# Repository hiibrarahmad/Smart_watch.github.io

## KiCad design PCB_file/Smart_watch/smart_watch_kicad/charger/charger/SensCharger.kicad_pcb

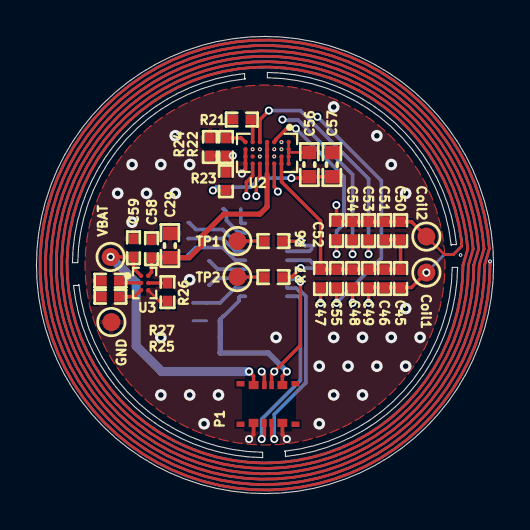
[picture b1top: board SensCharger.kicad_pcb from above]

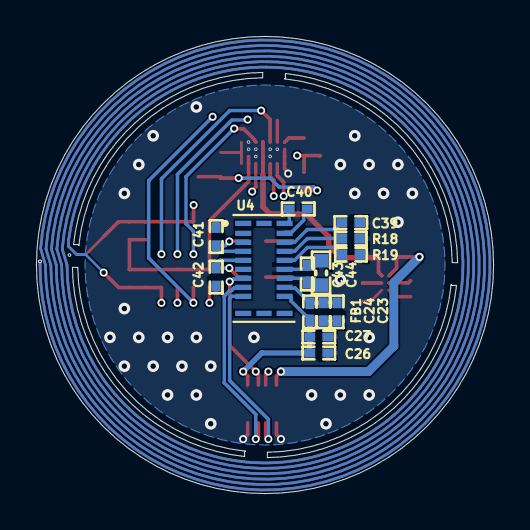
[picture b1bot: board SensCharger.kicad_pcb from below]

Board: 4 copper layers, 25.4 x 25.4 mm, 48 parts (14 on the bottom side), 34 nets.

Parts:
C23, C26, C43, C58: 100nF; C0402
C24, C27: 4.7uF; C0402
C29: 2.2uF; C0603
C39, C40, C59: 1uF; C0402
C41, C42: 10pF; C0402
C44, C56: 10uF; C0603
C45: 47nF; C0402
C46, C49: 68nF; C0402
C47, C53: 22nF; C0402
C48, C52: 10nF; C0402
C50: 1.8nF; C0402
C51: 100pF; C0402
C54, C55: 470nF; C0402
C57: 4.7uF; C0603
Coil1, Coil2: DNP; TP_SMD_1.0mm
FB1: BLM15AX102SN1D; IND0402
GND: DNP; TP_SMD_1.0mm
P1: 5050040812
R6, R7: 50K; RES0402
R18, R19: 0R; RES0402
R21, R25, R27: 10K; RES0402
R22: 845R; RES0402
R23: 20K; RES0402
R24: 196R; RES0402
R26: 1K; RES0402
TP1, TP2: DNP; TP_SMD_1.0mm
U2: BQ51003YFPR; BQ51003
U3: BQ25100YFPT; BQ25100YFP
U4: MAX86150EFF+T; MAX86150EFF+
VBAT: DNP; TP_SMD_1.0mm

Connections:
1V8: C26.2, C27.2, FB1.2, P1.5, U4.13
3V3: C43.2, C44.2, U4.15
CHG: P1.7, U2.F4
COIL: C45.2, C46.2, C49.2, C50.2, C51.2, C52.2, C53.2, C54.2, Coil1.1, Coil2.1, U2.B1, U2.B2
GND: C23.1, C24.1, C26.1, C27.1, C29.2, C39.2, C41.1, C42.1, C43.1, C44.1, C56.2, C57.2, C58.2, C59.2, GND.1, P1.1, P1.4, R18.2, R19.2, R21.1, R24.1, R25.1, R26.1, R27.1, U2.A1, U2.A2, U2.A3, U2.A4, U2.G2, U2.G3, U2.G4, U3.C2, U4.16
INT3: P1.6, U4.7
NetC23_2: C23.2, C24.2, FB1.1, U4.14
NetC39_1: C39.1, U4.19
NetC40_1: C40.1, U4.20
NetC40_2: C40.2, U4.21
NetC41_2: C41.2, R6.2, U4.4
NetC42_2: C42.2, R7.2, U4.5
NetC45_1: C45.1, C46.1, C47.2, C48.2, C49.1, C50.1, C51.1, C55.2, U2.B3, U2.B4
NetC47_1: C47.1, U2.E4
NetC48_1: C48.1, U2.C4
NetC52_1: C52.1, U2.C1
NetC53_1: C53.1, U2.E1
NetC54_1: C54.1, U2.E2
NetC55_1: C55.1, U2.E3
NetR6_1: R6.1, TP1.1
NetR7_1: R7.1, TP2.1
NetR18_1: R18.1, U4.18
NetR19_1: R19.1, U4.17
NetR21_2: R21.2, U2.F1
NetR22_1: R22.1, R23.1, R24.2, U2.F2
NetR22_2: R22.2, U2.G1
NetR25_2: R25.2, U3.C1
NetR26_2: R26.2, U3.B2
NetR27_2: R27.2, U3.B1
Rect: C56.1, C57.1, R23.2, U2.C2, U2.C3
SCL: P1.2, U4.9
SDA: P1.3, U4.8
VBAT: C59.1, P1.8, U3.A1, VBAT.1
Wvdd: C29.1, C58.1, U2.D1, U2.D2, U2.D3, U2.D4, U3.A2

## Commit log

2025-06-16 try1
2025-06-16 working
